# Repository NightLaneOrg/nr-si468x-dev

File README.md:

# 📡 Night Ride - Si468x Module

Open-source DAB/FM receiver module based on the **Silicon Labs / Skyworks Si468x series**.

This project provides hardware, software, and documentation to integrate a modern digital radio receiver into automotive and embedded Linux systems.

---

## Overview

The Si468x is a highly integrated broadcast receiver supporting:

- **DAB / DAB+**
- **FM (RDS)**
- Digital audio output via **I2S**
- Control via **I2C**

This repository focuses on building an **open and reusable platform** around the chip.

---

## Features

- Custom **M.2 E-Key module** design
- Automotive-oriented integration (infotainment systems)
- Linux driver / userspace control (WIP)
- Modular and reusable hardware design

---

## Repository Structure

```
/pcb        -> KiCad schematics & PCB layouts
/driver     -> Linux driver / interface code (WIP)
/tools      -> debugging and testing utilities
/firmware   -> placeholder (not included, see below)
```

---

## ⚠️ Firmware Notice

The Si468x requires proprietary firmware provided by the vendor.

❌ Firmware is **NOT included** in this repository  
❌ Redistribution is **not permitted**

See [`/firmware/README.md`](firmware/README.md) for details on how to obtain and use firmware.

---

## Hardware

> [!CAUTION]
> The PCBs till at least Commit ``9c4ef1d`` have I2S interferance issues, as is to hear [here](https://hut9.de/radio_audio)  
> This may have been fix in the later commits, but i don't have an later revision to this point
> so assume I2S will sound like that!  
> If someone knows how to fix that, feel free to contact me.

current design goals:

- Si4689-based RF frontend
- M.2 E-Key form factor
- External antenna support
- I2S digital audio output
- I2C host interface

[View Schematic & PCB](https://hut9.de/pcbs/nr-si468x-dev/)<br>
[View Schematic & PCB for the RPi adapter Hat](https://hut9.de/pcbs/nr-si468x-rpi-adapter/)

---

## Software

Planned features:

- Linux integration (userspace or kernel driver)
- Station tuning and service selection
- DAB / FM metadata parsing
- Integration into infotainment systems

---

## Documentation

Due to licensing restrictions, some vendor documentation is not included.

You may need to obtain:
- Programming guides
- Firmware files
- Additional application notes

These are typically available via:
- Community forums
- Existing development kits

---

## Status

🚧 Work in progress

- PCB: finished
- Driver: pending
- Testing: pending

---

## Licensing

This repository contains multiple components under different licenses:

- **Software (`/driver`, `/tools`)**  
  Licensed under the GNU General Public License v3.0 (GPL-3.0)

- **Hardware (`/pcb`)**  
  Licensed under the CERN Open Hardware License v2 - Strongly Reciprocal (CERN-OHL-S-2.0)

- **Firmware**  
  Not included. Proprietary and subject to vendor licensing.

See the individual folders for more details.

---

## 🌙 Night Lane

Part of the Night Lane open-source automotive platform.

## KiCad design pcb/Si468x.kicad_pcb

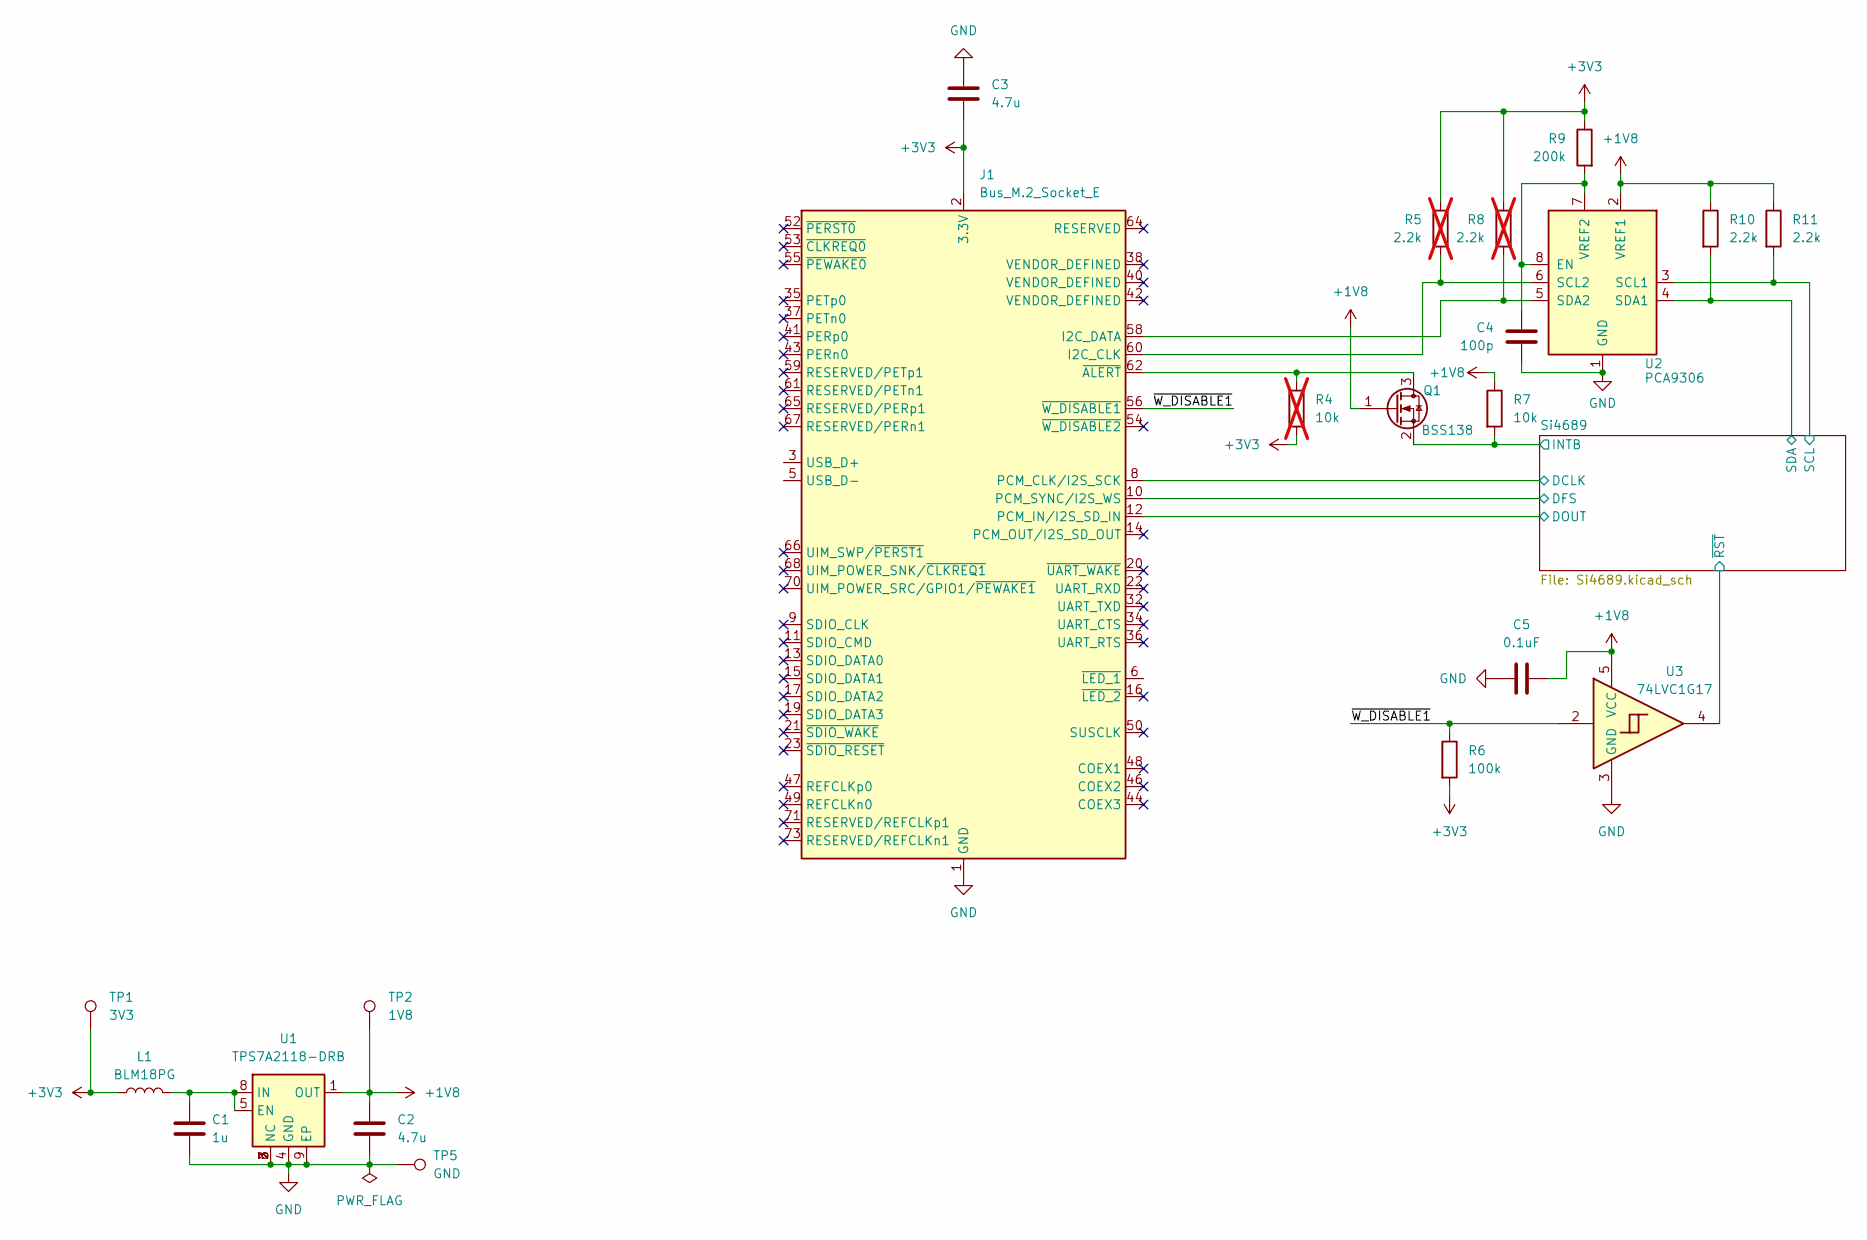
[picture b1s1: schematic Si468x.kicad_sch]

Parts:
C1: 1u; C_0603_1608Metric; LCSC C29936
C2, C3: 4.7u; C_0603_1608Metric; LCSC C18185770
C4: 100p; C_0402_1005Metric; LCSC C281751
C5: 0.1uF; C_0402_1005Metric; LCSC C77020
J1: Bus_M.2_Socket_E; M.2_2230-xx-E
L1: BLM18PG; L_0603_1608Metric; LCSC C80165
Q1: BSS138; SOT-23; LCSC C82045
R4: 10k; R_0402_1005Metric; LCSC C60490; not fitted
R5, R8: 2.2k; R_0402_1005Metric; LCSC C114762; not fitted
R6: 100k; R_0402_1005Metric; LCSC C60491
R7: 10k; R_0402_1005Metric; LCSC C60490
R9: 200k; R_0402_1005Metric; LCSC C60490
R10, R11: 2.2k; R_0402_1005Metric; LCSC C114762
TP1: 3V3; TestPoint_Pad_D1.0mm
TP2: 1V8; TestPoint_Pad_D1.0mm
TP5: GND; TestPoint_Pad_D1.0mm
U1: TPS7A2118-DRB; Texas_DRB_VSON_8; LCSC C35469250
U2: PCA9306; VSSOP-8_2.3x2mm_P0.5mm
U3: 74LVC1G17; Texas_R-PDSO-G5_DCK-5; LCSC C10425

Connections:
+1V8: C2.1, C5.2, Q1.1 (G), R7.1, R10.1, R11.1, TP2.1 (1_1), U1.1 (OUT), U2.2 (VREF1), U3.5 (VCC); also elsewhere on the board
+3V3: C3.2, J1.2 (3.3V), J1.4 (3.3V), J1.72 (3.3V), J1.74 (3.3V), L1.1, R4.2, R5.1, R6.2, R8.1, R9.1, TP1.1 (1_1)
/Si4689/DCLK: J1.8 (PCM_CLK/I2S_SCK); also elsewhere on the board
/Si4689/DFS: J1.10 (PCM_SYNC/I2S_WS); also elsewhere on the board
/Si4689/DOUT: J1.12 (PCM_IN/I2S_SD_IN); also elsewhere on the board
/Si4689/INTB: Q1.2 (S), R7.2; also elsewhere on the board
/Si4689/SCL: R11.2, U2.3 (SCL1); also elsewhere on the board
/Si4689/SDA: R10.2, U2.4 (SDA1); also elsewhere on the board
/Si4689/~RST: U3.4; also elsewhere on the board
/~W_DISABLE1: J1.56 (~W_DISABLE1), R6.1, U3.2
GND: C1.2, C2.2, C3.1, C4.2, C5.1, J1.1 (GND), J1.7 (GND), J1.18 (GND), J1.33 (GND), J1.39 (GND), J1.45 (GND), J1.51 (GND), J1.57 (GND), J1.63 (GND), J1.69 (GND), J1.75 (GND), TP5.1 (1_1), U1.2 (NC), U1.3 (NC), U1.4 (GND), U1.6 (NC), U1.7 (NC), U1.9 (EP), U2.1 (GND), U3.3 (GND); also elsewhere on the board
unnamed: J1.60 (I2C_CLK), R5.2, U2.6 (SCL2)
unnamed: J1.58 (I2C_DATA), R8.2, U2.5 (SDA2)
unnamed: J1.62 (~ALERT), Q1.3 (D), R4.1
unnamed: C1.1, L1.2, U1.5 (EN), U1.8 (IN)
unnamed: C4.1, R9.2, U2.7 (VREF2), U2.8 (EN)

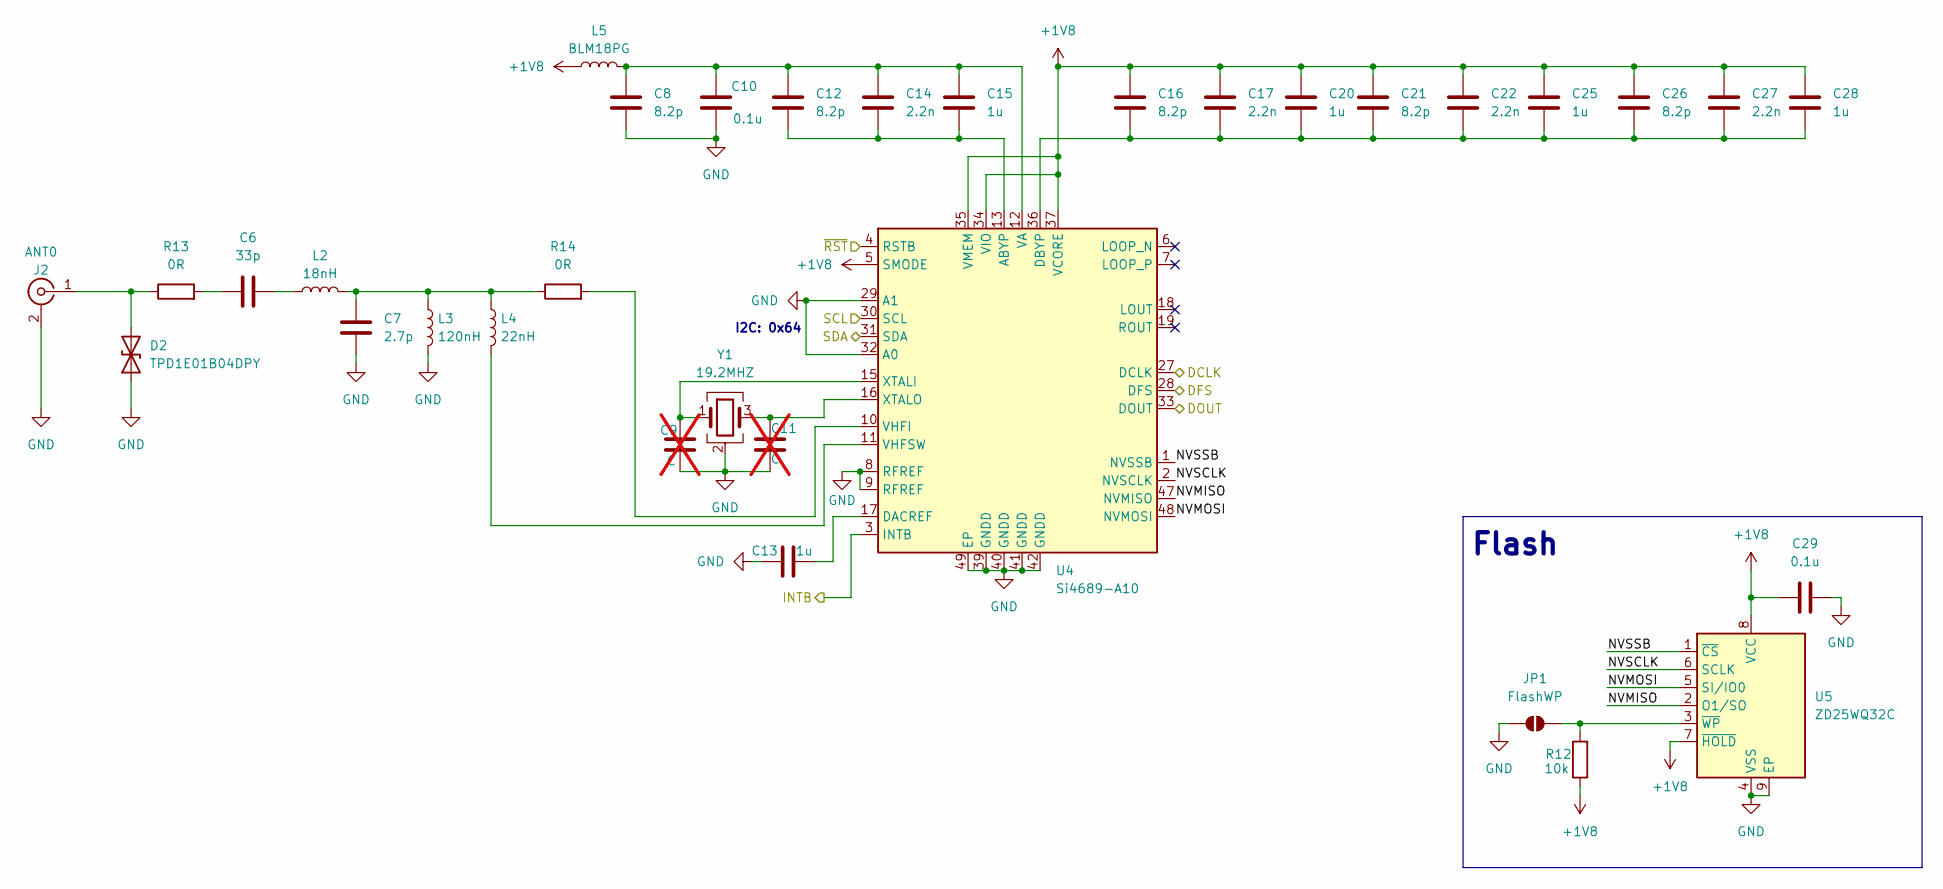
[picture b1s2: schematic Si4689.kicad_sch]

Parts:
C6: 33p; C_0402_1005Metric; LCSC C70465
C7: 2.7p; C_0402_1005Metric; LCSC C76904
C8, C12, C16, C21, C26: 8.2p; C_0402_1005Metric; LCSC C76984
C9, C11: C; C_0402_1005Metric; not fitted
C10, C29: 0.1u; C_0402_1005Metric; LCSC C77020
C13, C15, C20, C25, C28: 1u; C_0402_1005Metric; LCSC C576449
C14, C17, C22, C27: 2.2n; C_0402_1005Metric; LCSC C126534
D2: TPD1E01B04DPY; Texas_DPY0002A_0.6x1mm_P0.65mm; LCSC C779389
J2: ANT0; IPEX_20449-001E-03; LCSC C784401
JP1: FlashWP; SolderJumper-2_P1.3mm_Open_RoundedPad1.0x1.5mm
L2: 18nH; L_0402_1005Metric; LCSC C668381
L3: 120nH; L_0402_1005Metric; LCSC C113123
L4: 22nH; L_0402_1005Metric; LCSC C703122
L5: BLM18PG; L_0603_1608Metric; LCSC C80165
R12: 10k; R_0402_1005Metric; LCSC C60490
R13, R14: 0R; R_0402_1005Metric; LCSC C106231
U4: Si4689-A10; QFN-48_EP_7x7_Pitch0.5mm; LCSC C1526087
U5: ZD25WQ32C; Winbond_USON-8-1EP_3x2mm_P0.5mm_EP0.2x1.6mm; LCSC C5258281
Y1: 19.2MHZ; Crystal_SMD_3225-4Pin_3.2x2.5mm; LCSC C1986852

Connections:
+1V8: C16.1, C17.1, C20.1, C21.1, C22.1, C25.1, C26.1, C27.1, C28.1, C29.1, L5.1, R12.1, U4.5 (SMODE), U4.34 (VIO), U4.35 (VMEM), U4.37 (VCORE), U5.7 (~HOLD), U5.8 (VCC); also elsewhere on the board
/Si4689/DCLK: U4.27 (DCLK); also elsewhere on the board
/Si4689/DFS: U4.28 (DFS); also elsewhere on the board
/Si4689/DOUT: U4.33 (DOUT); also elsewhere on the board
/Si4689/INTB: U4.3 (INTB); also elsewhere on the board
/Si4689/NVMISO: U4.47 (NVMISO), U5.2 (O1/SO)
/Si4689/NVMOSI: U4.48 (NVMOSI), U5.5 (SI/IO0)
/Si4689/NVSCLK: U4.2 (NVSCLK), U5.6 (SCLK)
/Si4689/NVSSB: U4.1 (NVSSB), U5.1 (~CS)
/Si4689/SCL: U4.30 (SCL); also elsewhere on the board
/Si4689/SDA: U4.31 (SDA); also elsewhere on the board
/Si4689/~RST: U4.4 (RSTB); also elsewhere on the board
GND: C7.2, C8.2, C9.2, C10.2, C11.2, C13.1, C29.2, D2.1 (A1), J2.2 (Ext), JP1.1 (A), L3.2, U4.8 (RFREF), U4.9 (RFREF), U4.29 (A1), U4.32 (A0), U4.39 (GNDD), U4.40 (GNDD), U4.41 (GNDD), U4.42 (GNDD), U4.49 (EP), U5.4 (VSS), U5.9 (EP), Y1.2 (G), Y1.4 (G); also elsewhere on the board
unnamed: C6.1, R13.2
unnamed: C6.2, L2.1
unnamed: C7.1, L2.2, L3.1, L4.1, R14.1
unnamed: D2.2 (A2), J2.1 (In), R13.1
unnamed: JP1.2 (B), R12.2, U5.3 (~WP)
unnamed: C12.2, C14.2, C15.2, U4.13 (ABYP)
unnamed: C13.2, U4.17 (DACREF)
unnamed: C16.2, C17.2, C20.2, C21.2, C22.2, C25.2, C26.2, C27.2, C28.2, U4.36 (DBYP)
unnamed: C8.1, C10.1, C12.1, C14.1, C15.1, L5.2, U4.12 (VA)
unnamed: R14.2, U4.10 (VHFI)
unnamed: L4.2, U4.11 (VHFSW)
unnamed: C9.1, U4.15 (XTALI), Y1.1
unnamed: C11.1, U4.16 (XTALO), Y1.3

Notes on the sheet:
I2C: 0x64
Flash

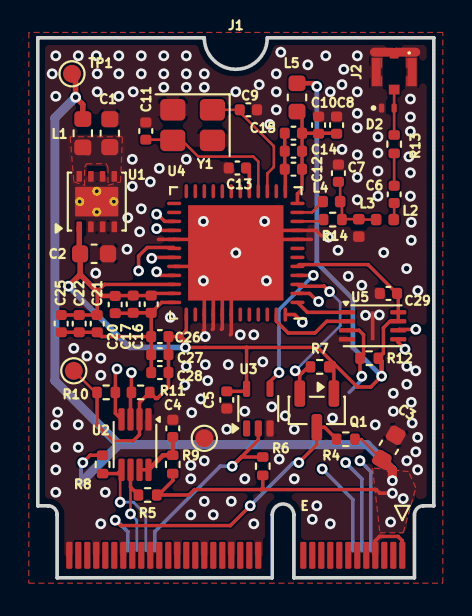
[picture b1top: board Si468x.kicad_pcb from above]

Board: 4 copper layers, 22.0 x 30.0 mm, 55 parts (1 on the bottom side), 33 nets.

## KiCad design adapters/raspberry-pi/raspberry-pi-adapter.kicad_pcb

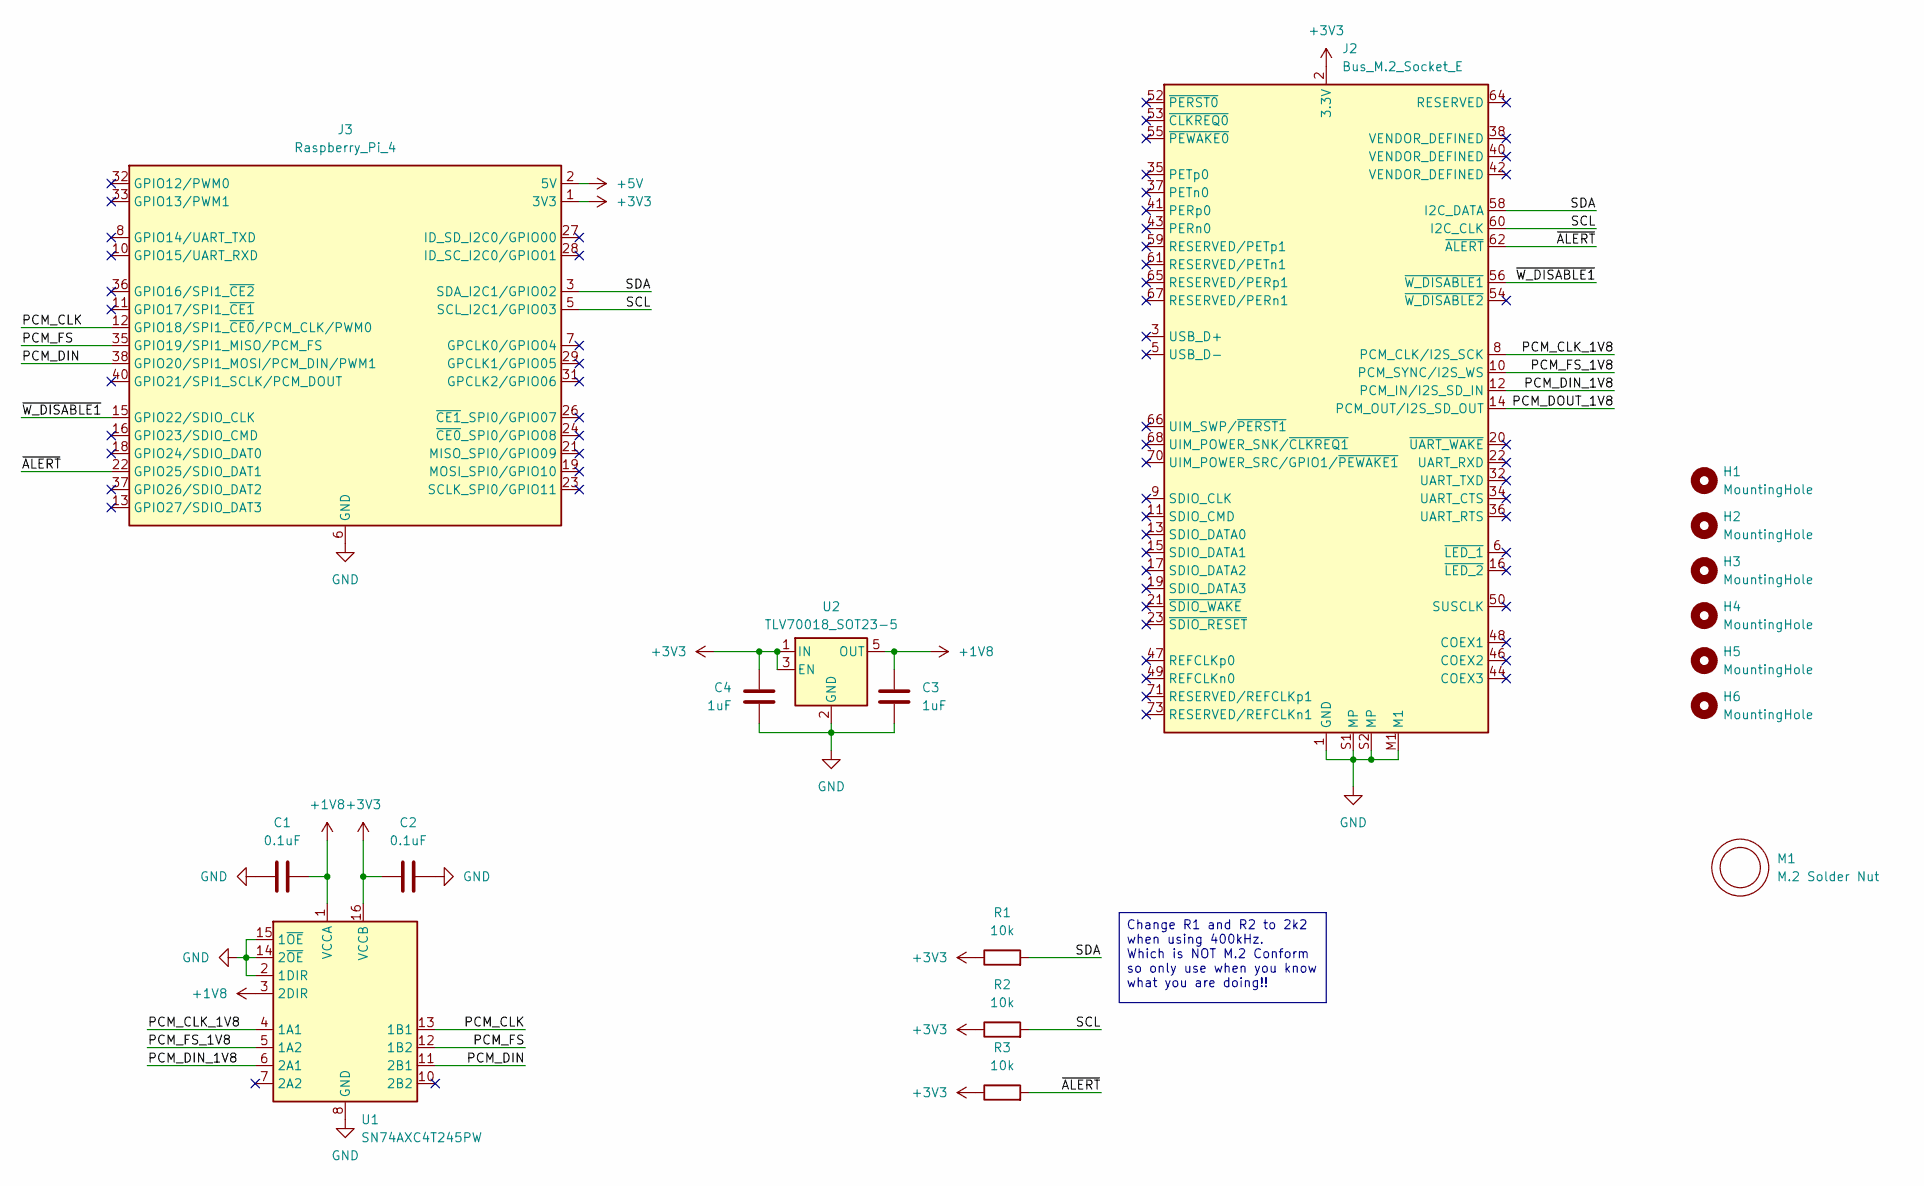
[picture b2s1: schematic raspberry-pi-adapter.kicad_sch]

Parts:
C1, C2: 0.1uF; C_0603_1608Metric; LCSC C14663
C3, C4: 1uF; C_0603_1608Metric; LCSC C15849
H1, H2, H3, H4, H5, H6: MountingHole; MountingHole_2.7mm_M2.5
J2: Bus_M.2_Socket_E; JAE_SM3ZS067U310AER1200; LCSC C4755078
J3: Raspberry_Pi_4
M1: M.2 Solder Nut; LCSC C5221772
R1, R2, R3: 10k; R_0603_1608Metric; LCSC C25804
U1: SN74AXC4T245PW; TSSOP-16_4.4x5mm_P0.65mm; LCSC C2867798
U2: TLV70018_SOT23-5; SOT-23-5; LCSC C79924

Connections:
+1V8: C1.1, C3.1, U1.1 (VCCA), U1.3 (2DIR), U2.5 (OUT)
+3V3: C2.2, C4.1, J2.2 (3.3V), J2.4 (3.3V), J2.72 (3.3V), J2.74 (3.3V), J3.1 (3V3), J3.17 (3V3), R1.1, R2.1, R3.1, U1.16 (VCCB), U2.1 (IN), U2.3 (EN)
+5V: J3.2 (5V), J3.4 (5V)
/PCM_CLK: J3.12 (GPIO18/SPI1_~CE0/PCM_CLK/PWM0), U1.13 (1B1)
/PCM_CLK_1V8: J2.8 (PCM_CLK/I2S_SCK), U1.4 (1A1)
/PCM_DIN: J3.38 (GPIO20/SPI1_MOSI/PCM_DIN/PWM1), U1.11 (2B1)
/PCM_DIN_1V8: J2.12 (PCM_IN/I2S_SD_IN), U1.6 (2A1)
/PCM_DOUT_1V8: J2.14 (PCM_OUT/I2S_SD_OUT)
/PCM_FS: J3.35 (GPIO19/SPI1_MISO/PCM_FS), U1.12 (1B2)
/PCM_FS_1V8: J2.10 (PCM_SYNC/I2S_WS), U1.5 (1A2)
/SCL: J2.60 (I2C_CLK), J3.5 (SCL_I2C1/GPIO03), R2.2
/SDA: J2.58 (I2C_DATA), J3.3 (SDA_I2C1/GPIO02), R1.2
/~ALERT: J2.62 (~ALERT), J3.22 (GPIO25/SDIO_DAT1), R3.2
/~W_DISABLE1: J2.56 (~W_DISABLE1), J3.15 (GPIO22/SDIO_CLK)
GND: C1.2, C2.1, C3.2, C4.2, J2.1 (GND), J2.7 (GND), J2.18 (GND), J2.33 (GND), J2.39 (GND), J2.45 (GND), J2.51 (GND), J2.57 (GND), J2.63 (GND), J2.69 (GND), J2.75 (GND), J2.M1, J2.S1 (MP), J2.S2 (MP), J3.6 (GND), J3.9 (GND), J3.14 (GND), J3.20 (GND), J3.25 (GND), J3.30 (GND), J3.34 (GND), J3.39 (GND), U1.2 (1DIR), U1.8 (GND), U1.9 (GND), U1.14 (2~OE), U1.15 (1~OE), U2.2 (GND)

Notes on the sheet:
Change R1 and R2 to 2k2 when using 400kHz. Which is NOT M.2 Conform so only use when you know what you are doing!!

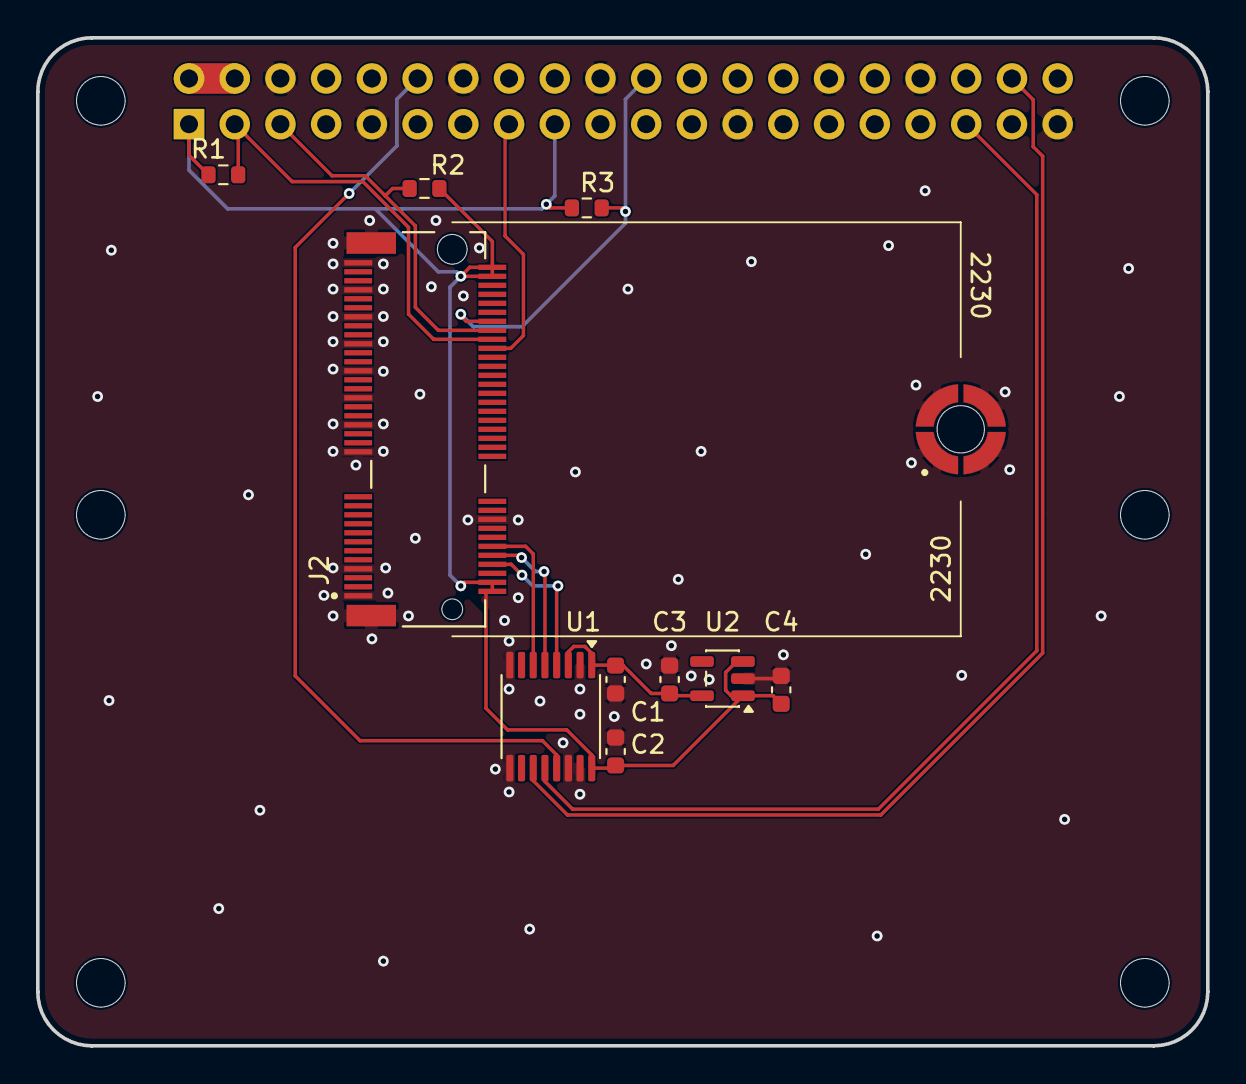
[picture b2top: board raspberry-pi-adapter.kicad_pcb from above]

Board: 2 copper layers, 65.0 x 56.0 mm, 17 parts (1 on the bottom side), 14 nets.

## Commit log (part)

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2026-05-27 Update README with additional firmware resource link
    Added a link to the MustangRadio development version repository.
2026-05-27 Enhance README with new example link and formatting
    Updated README with additional example link and formatting.
